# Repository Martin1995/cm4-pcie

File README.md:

# cm4-pcie
TODO:
-Connect HPD of HDMI In to the right pin on the Toshiba HDMI CSI-2 bridge

Feel free to copy the design, I'm not a Highspeed PCB expert, but if you want to use this PCB Design, to create a PCIe Card sized Raspberry Pi CM4 Carrier Board that can plug in to a PCIe Backplane feel free to do so.

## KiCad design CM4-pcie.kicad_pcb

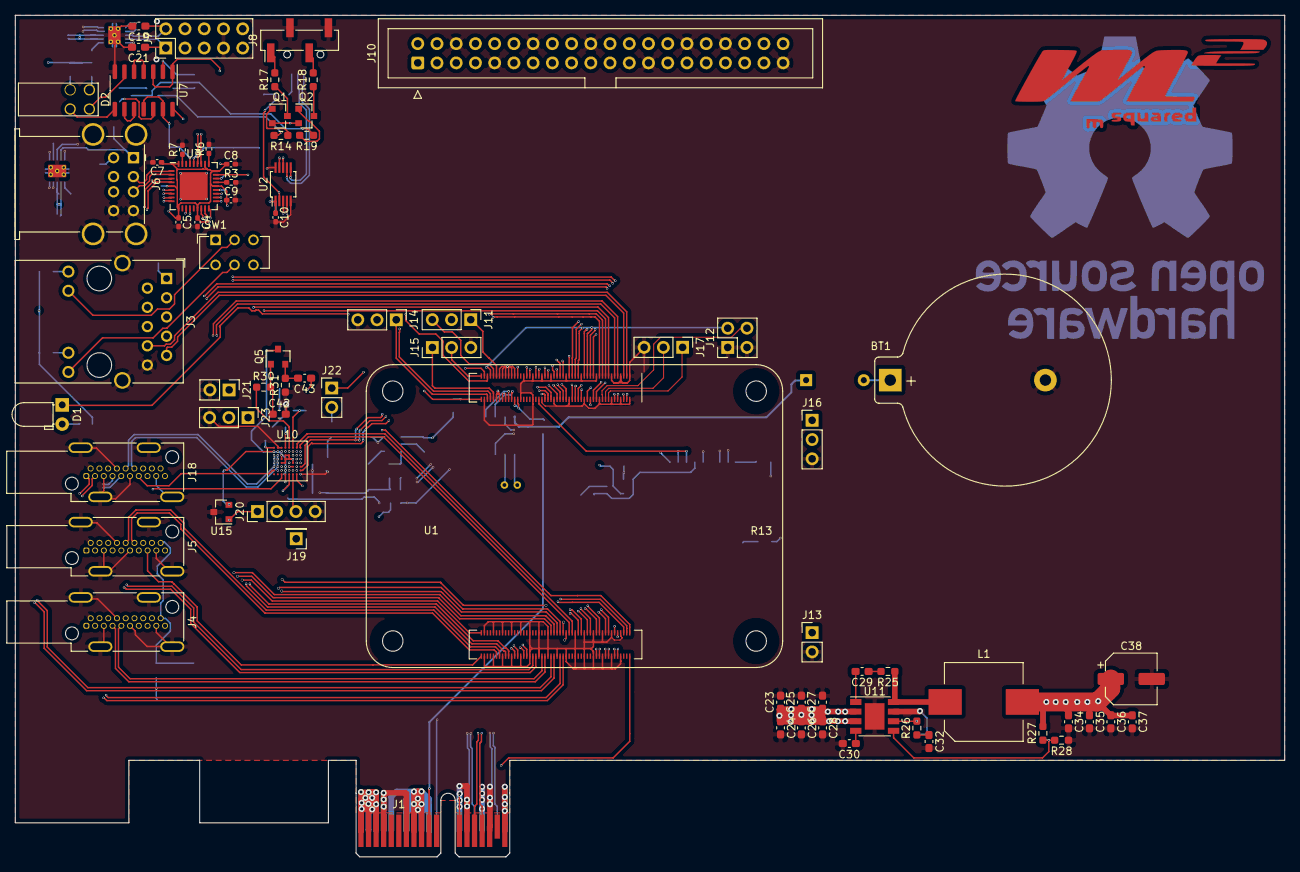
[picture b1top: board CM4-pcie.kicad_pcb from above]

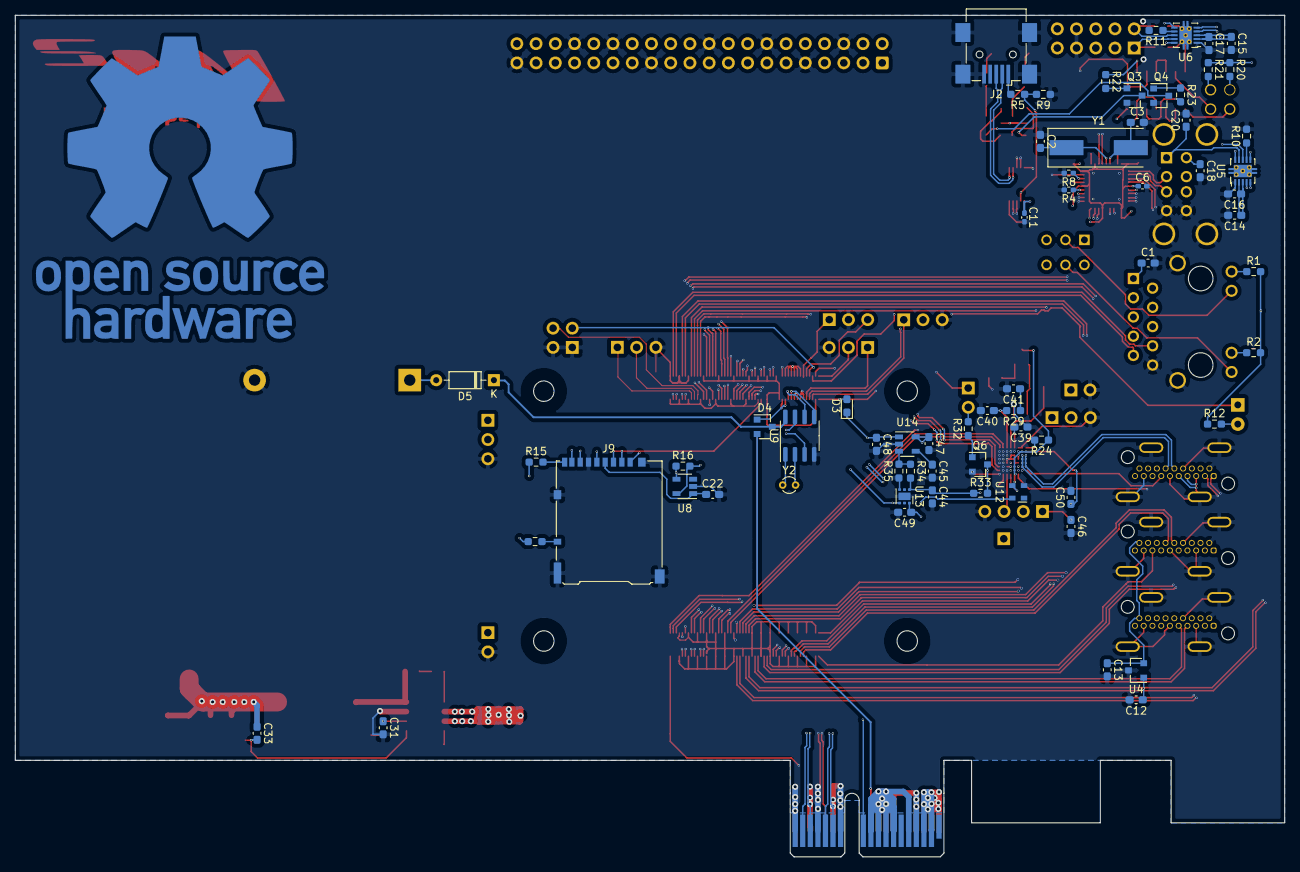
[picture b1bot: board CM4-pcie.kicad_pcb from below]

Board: 6 copper layers, 167.7 x 111.2 mm, 139 parts (66 on the bottom side), 226 nets.

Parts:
BT1: Battery_Cell; BatteryHolder_Keystone_106_1x20mm
C1: C; C_0603_1608Metric_Pad1.08x0.95mm_HandSolder
C2, C3: 27pF; C_0603_1608Metric_Pad1.08x0.95mm_HandSolder
C4, C5: 10µ; C_0402_1005Metric_Pad0.74x0.62mm_HandSolder
C6, C7, C8, C9, C10, C11: 100n; C_0402_1005Metric_Pad0.74x0.62mm_HandSolder
C12, C13, C29, C30: 100n; C_0603_1608Metric_Pad1.08x0.95mm_HandSolder
C14, C15, C16, C17, C18, C19, C20, C21, C22, C23, C24, C25, C26, C27, C28, C34, C35, C36, C37: 10µ; C_0603_1608Metric_Pad1.08x0.95mm_HandSolder
C31, C33: nf; C_0603_1608Metric_Pad1.08x0.95mm_HandSolder
C32: 1.2nF; C_0603_1608Metric_Pad1.08x0.95mm_HandSolder
C38: 100µF; CP_Elec_6.3x5.4_Nichicon
C39, C41: 0.1µF; C_0603_1608Metric_Pad1.08x0.95mm_HandSolder
C40, C43: 1000pF; C_0603_1608Metric_Pad1.08x0.95mm_HandSolder
C42: 5pF; C_0603_1608Metric_Pad1.08x0.95mm_HandSolder
C44, C46, C47, C48, C49, C50: 1µ; C_0603_1608Metric_Pad1.08x0.95mm_HandSolder
C45: 0.1µ; C_0603_1608Metric_Pad1.08x0.95mm_HandSolder
D1: LED; LED_D3.0mm_Horizontal_O1.27mm_Z2.0mm
D2: LED_Dual_AACC; DIAL_553-0112-20
D3: D; D_0603_1608Metric_Pad1.05x0.95mm_HandSolder
D4: BAT54C; SOT-23
D5: D_Schottky; D_DO-35_SOD27_P7.62mm_Horizontal
J1: Bus_PCI_Express_x1; BUS_PCIexpress_x1
J2: USB_B_Micro; USB_Mini-B_Wuerth_65100516121_Horizontal
J3: RB1-125B8G1A; RJ45_Wuerth_7499111446_Horizontal
J4, J5, J18: HDMI_A_1.4; HDMI_A_Kycon_KDMIX-SL1-NS-WS-B15_VerticalRightAngle
J6: USB_A; USB_A_Wuerth_61400826021_Horizontal_Stacked
J7: Conn_02x05_Odd_Even; PinHeader_2x05_P2.54mm_Vertical
J8: Conn_01x04; PinHeader_1x04_P2.54mm_Vertical_SMD_Pin1Left
J9: Micro_SD_Card_Det_Hirose_DM3AT; microSD_HC_Hirose_DM3AT-SF-PEJM5
J10: Raspberry_Pi_2_3; IDC-Header_2x20_P2.54mm_Vertical
J11, J14, J15, J16, J17, J23: Conn_01x03; PinHeader_1x03_P2.54mm_Vertical
J12: Conn_02x02_Odd_Even; PinHeader_2x02_P2.54mm_Vertical
J13, J21, J22: Conn_01x02; PinHeader_1x02_P2.54mm_Vertical
J19: Conn_01x01; PinHeader_1x01_P2.54mm_Vertical
J20: Conn_01x04; PinHeader_1x04_P2.54mm_Vertical
L1: 3.6µH WE7447797360; L_Wuerth_WE-PDF_Handsoldering
Q1, Q2: BC857; SOT-23
Q3, Q4, Q5, Q6: BC847; SOT-23
R1, R2, R12, R17, R18, R20, R21: 470R; R_0603_1608Metric_Pad0.98x0.95mm_HandSolder
R3, R4, R6, R8: 36k; R_0402_1005Metric_Pad0.72x0.64mm_HandSolder
R5, R9, R28: 2k2; R_0603_1608Metric_Pad0.98x0.95mm_HandSolder
R7: 12k; R_0402_1005Metric_Pad0.72x0.64mm_HandSolder
R10, R11: 28k; R_0603_1608Metric_Pad0.98x0.95mm_HandSolder
R13, R15: nf; R_0603_1608Metric_Pad0.98x0.95mm_HandSolder
R14, R19, R22, R23, R29, R31, R32, R33, R34, R35: 1k; R_0603_1608Metric_Pad0.98x0.95mm_HandSolder
R16: 12k; R_0603_1608Metric_Pad0.98x0.95mm_HandSolder
R24: 2k; R_0603_1608Metric_Pad0.98x0.95mm_HandSolder
R25: 10R; R_0603_1608Metric_Pad0.98x0.95mm_HandSolder
R26: 20k; R_0603_1608Metric_Pad0.98x0.95mm_HandSolder
R27: 10k; R_0603_1608Metric_Pad0.98x0.95mm_HandSolder
R30: 1k5; R_0603_1608Metric_Pad0.98x0.95mm_HandSolder
SW1: SW_DPDT_x2; SW_CuK_JS202011AQN_DPDT_Angled
U1: Compute_Module_4_Functional; Raspberry-Pi-4-Compute-Module
U2: FSUSB42MUX; MSOP-10_3x3mm_P0.5mm
U3: USB2514B_Bi; QFN-36-1EP_6x6mm_P0.5mm_EP3.7x3.7mm
U4, U15: RT9742SNGV; SOT-23
U5, U6: TPS2561; VSON-10-1EP_3x3mm_P0.5mm_EP1.65x2.4mm_ThermalVias
U7: 74HC04; SO-14_3.9x8.65mm_P1.27mm
U8: RT9742GGJ5; SOT-23-5
U9: PCF8563T; SOIC-8_3.9x4.9mm_P1.27mm
U10: TC358743XBG; TFBGA-64_5x5mm_Layout8x8_P0.5mm
U11: AP64501SP-13; Diodes_SO-8EP
U12: ASDMB-xxxMHz; Oscillator_SMD_Abracon_ASDMB-4Pin_2.5x2.0mm
U13: TLV75512PDRV; WSON-6-1EP_2x2mm_P0.65mm_EP1x1.6mm
U14: TC2015-2.5VxCTTR; SOT-23-5
Y1: Crystal; Crystal_SMD_HC49-SD
Y2: Crystal; Crystal_Round_D1.5mm_Vertical

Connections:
+1V2: C44.1, R33.1, R34.2, U10.B2, U10.C3, U10.C6, U10.D3, U10.F5, U10.F6, U10.G2, U13.1
+1V8: U1.88, U1.90, U12.4, U13.4
+2V5: C47.1, U10.B5, U14.5
+3.3VA: D4.2, J1.B10
+3V3: C4.1, C5.1, C6.1, C7.1, C8.1, C9.1, C10.1, C11.1, C46.1, C48.1, C49.1, D3.1, D4.1, J1.A5, J1.A7, J1.A8, J1.A9, J1.A10, J1.B8, J1.B9, J10.1, J10.17, J20.1, Q1.2, Q2.2, Q5.3, R1.2, R2.2, R12.1, R13.1, R16.2, R20.1, R21.1, R24.1, U1.78, U2.1, U3.5, U3.10, U3.15, U3.23, U3.27, U3.29, U3.36, U7.14, U8.5, U10.F4, U10.H7, U13.6, U14.1, U15.1
+3V3-HDMI: C50.1, U10.B1, U10.F3, U15.2
+5V: C12.1, C14.1, C15.1, C16.1, C17.1, C33.1, C34.1, C35.1, C36.1, C37.1, C38.1, J10.2, J10.4, L1.2, R27.2, U1.77, U1.79, U1.81, U1.83, U1.85, U1.87, U4.1, U5.2, U5.3, U6.2, U6.3
+12V: C23.1, C24.1, C25.1, C26.1, C27.1, C28.1, J1.A2, J1.A3, J1.B1, J1.B2, J1.B3, U11.2, U11.3
+BATT: BT1.1, D5.2
/LAN_LED1: D1.1, U1.19
/LAN_LED2: SW1.3, SW1.4, U1.17
/LAN_LED3: SW1.1, SW1.6, U1.15
/PCIe_CLK_N: J1.A14, U1.112
/PCIe_CLK_P: J1.A13, U1.110
/PCIe_RX_N: J1.A17, U1.118
/PCIe_RX_P: J1.A16, U1.116
/PCIe_TX_N: J1.B15, U1.124
/PCIe_TX_P: J1.B14, U1.122
/RJ45_LED1: J3.12, SW1.2
/RJ45_LED2: J3.14, SW1.5
/Sheet606D5A30/CM_USB_D+: U1.105, U2.3
/Sheet606D5A30/CM_USB_D-: U1.103, U2.4
/Sheet606D5A30/CM_USB_OTG: R5.1, R9.2, U1.101, U2.2
/Sheet606D5A30/HDMI0_CEC: J5.13, U1.151
/Sheet606D5A30/HDMI0_CLK_N: J5.12, U1.190
/Sheet606D5A30/HDMI0_CLK_P: J5.10, U1.188
/Sheet606D5A30/HDMI0_D0_N: J5.9, U1.184
/Sheet606D5A30/HDMI0_D0_P: J5.7, U1.182
/Sheet606D5A30/HDMI0_D1_N: J5.6, U1.178
/Sheet606D5A30/HDMI0_D1_P: J5.4, U1.176
/Sheet606D5A30/HDMI0_D2_N: J5.3, U1.172
/Sheet606D5A30/HDMI0_D2_P: J5.1, U1.170
/Sheet606D5A30/HDMI0_HOTPLUG: J5.19, U1.153
/Sheet606D5A30/HDMI0_SCL: J5.15, U1.200
/Sheet606D5A30/HDMI0_SDA: J5.16, U1.199
/Sheet606D5A30/HDMI1_CEC: J4.13, U1.149
/Sheet606D5A30/HDMI1_CLK_N: J4.12, U1.166
/Sheet606D5A30/HDMI1_CLK_P: J4.10, U1.164
/Sheet606D5A30/HDMI1_D0_N: J4.9, U1.160
/Sheet606D5A30/HDMI1_D0_P: J4.7, U1.158
/Sheet606D5A30/HDMI1_D1_N: J4.6, U1.154
/Sheet606D5A30/HDMI1_D1_P: J4.4, U1.152
/Sheet606D5A30/HDMI1_D2_N: J4.3, U1.148
/Sheet606D5A30/HDMI1_D2_P: J4.1, U1.146
/Sheet606D5A30/HDMI1_HOTPLUG: J4.19, U1.143
/Sheet606D5A30/HDMI1_SCL: J4.15, U1.147
/Sheet606D5A30/HDMI1_SDA: J4.16, U1.145
/Sheet606D5A30/HDMI_5v: C13.1, J4.18, J5.18, U4.2
/Sheet606D5A30/HUB_USB_D+: U2.9, U3.31
/Sheet606D5A30/HUB_USB_D-: U2.8, U3.30
/Sheet606D5A30/PROG_USB_D+: J2.3, U2.7
/Sheet606D5A30/PROG_USB_D-: J2.2, U2.6
/Sheet606D5A30/Sheet60CE0192/VBUS_P1: C20.1, J6.1, U5.9
/Sheet606D5A30/Sheet60CE0192/VBUS_P2: C18.1, J6.5, U5.8
/Sheet606D5A30/Sheet60CE0192/VBUS_P3: C21.1, J7.1, U6.9
/Sheet606D5A30/Sheet60CE0192/VBUS_P4: C19.1, J7.2, U6.8
/Sheet606E499F/BLUETOOTH_nDISABLE: J11.3, U1.91
/Sheet606E499F/EEPROM_nWP: J12.4, U1.20
/Sheet606E499F/RPI_ACT_LED: U1.21, U7.11, U7.13
/Sheet606E499F/RPI_PWR_LED: U1.95, U7.1, U7.3
/Sheet606E499F/Reserved: R15.1, U1.76
/Sheet606E499F/SD_CLK: J9.5, U1.57
/Sheet606E499F/SD_CMD: J9.3, U1.62
/Sheet606E499F/SD_DAT0: J9.7, U1.63
/Sheet606E499F/SD_DAT1: J9.8, U1.67
/Sheet606E499F/SD_DAT2: J9.1, U1.69
/Sheet606E499F/SD_DAT3: J9.2, U1.61
/Sheet606E499F/SD_PWR: C22.1, J9.4, U8.1
/Sheet606E499F/SD_PWR_ON: R16.1, U1.75, U8.4
/Sheet606E499F/WIRELESS_nDISABLE: J11.1, U1.89
/Sheet606E499F/nRPIBOOT: J12.2, U1.93
/Sheet611CBD44/CSI1_C_N: U1.127, U10.C7
/Sheet611CBD44/CSI1_C_P: U1.129, U10.C8
/Sheet611CBD44/CSI1_D0_N: U1.115, U10.E7
/Sheet611CBD44/CSI1_D0_P: U1.117, U10.E8
/Sheet611CBD44/CSI1_D1_N: U1.121, U10.D7
/Sheet611CBD44/CSI1_D1_P: U1.123, U10.D8
/Sheet611CBD44/CSI1_D2_N: U1.133, U10.B7
/Sheet611CBD44/CSI1_D2_P: U1.135, U10.B8
/Sheet611CBD44/CSI1_D3_N: U1.139, U10.A7
/Sheet611CBD44/CSI1_D3_P: U1.141, U10.A8
/Sheet611CBD44/HDMI_IN0_CEC: J18.13, U10.G1
/Sheet611CBD44/HDMI_IN0_CLK_N: J18.12, U10.C2
/Sheet611CBD44/HDMI_IN0_CLK_P: J18.10, U10.C1
/Sheet611CBD44/HDMI_IN0_D0_N: J18.9, U10.D2
/Sheet611CBD44/HDMI_IN0_D0_P: J18.7, U10.D1
/Sheet611CBD44/HDMI_IN0_D1_N: J18.6, U10.E2
/Sheet611CBD44/HDMI_IN0_D1_P: J18.4, U10.E1
/Sheet611CBD44/HDMI_IN0_D2_N: J18.3, U10.F2
/Sheet611CBD44/HDMI_IN0_D2_P: J18.1, U10.F1
/Sheet611CBD44/HDMI_IN0_EDID_SCL: J20.3, U10.H6
/Sheet611CBD44/HDMI_IN0_EDID_SDA: J20.2, U10.G6
/Sheet611CBD44/HDMI_IN0_HPD: J18.19, U10.H2
/Sheet611CBD44/HDMI_IN0_INT: J23.2, U10.B3
/Sheet611CBD44/HDMI_IN0_IR-IN: J21.1, U10.B4
/Sheet611CBD44/HDMI_IN0_SCL: J18.15, U10.H3
/Sheet611CBD44/HDMI_IN0_SDA: J18.16, U10.G3
/Sheet611CBD44/REFCLK0: U10.H5, U12.3
/Sheet611CBD44/RESETN: Q6.3, R33.2, U10.G5
/Sheet611CBD44/U10_BIASDA: C39.2, U10.A4
/Sheet611CBD44/U10_DAOUT: R30.1, U10.A5
/Sheet611CBD44/U10_PCKIN: C43.1, U10.B6
/Sheet611CBD44/U10_PFIL: C40.1, R29.2, U10.A6
/Sheet611CBD44/U10_TEST: J23.1, U10.E5
/Sheet6070FC9D/GPIO2: J10.3, U1.56
/Sheet6070FC9D/GPIO3: J10.5, U1.58
/Sheet6070FC9D/GPIO4: J10.7, U1.54
/Sheet6070FC9D/GPIO5: J10.29, U1.34
/Sheet6070FC9D/GPIO6: J10.31, U1.30
/Sheet6070FC9D/GPIO7: J10.26, U1.37
/Sheet6070FC9D/GPIO8: J10.24, U1.39
/Sheet6070FC9D/GPIO9: J10.21, U1.40
/Sheet6070FC9D/GPIO10: J10.19, U1.44
/Sheet6070FC9D/GPIO11: J10.23, U1.38
/Sheet6070FC9D/GPIO12: J10.32, U1.31
/Sheet6070FC9D/GPIO13: J10.33, U1.28
/Sheet6070FC9D/GPIO14: J10.8, U1.55
/Sheet6070FC9D/GPIO15: J10.10, U1.51
/Sheet6070FC9D/GPIO16: J10.36, U1.29
/Sheet6070FC9D/GPIO17: J10.11, U1.50
/Sheet6070FC9D/GPIO21: J10.40, U1.25
/Sheet6070FC9D/GPIO22: J10.15, U1.46
/Sheet6070FC9D/GPIO23: J10.16, U1.47
/Sheet6070FC9D/GPIO24: J10.18, U1.45
/Sheet6070FC9D/GPIO25: J10.22, U1.41
/Sheet6070FC9D/GPIO26: J10.37, U1.24
/Sheet6070FC9D/GPIO27: J10.13, U1.48
/Sheet6070FC9D/ID_SC: J10.28, U1.36
/Sheet6070FC9D/ID_SD: J10.27, U1.35
/TRD0_N: J3.3, U1.10
/TRD0_P: J3.2, U1.12
/TRD1_N: J3.5, U1.6
/TRD1_P: J3.4, U1.4
/TRD2_N: J3.7, U1.9
/TRD2_P: J3.6, U1.11
/TRD3_N: J3.9, U1.5
/TRD3_P: J3.8, U1.3
/__PCIe_CLK_nREQ: J1.B12, U1.102
/__PCIe_nRST: J1.A11, U1.109
AI0: J14.1, U1.96
AI1: J14.2, U1.94
CAM_GPIO: J22.1, U1.97
COMPOSITE: J13.1, U1.111
ETH_SYNC_IN: J17.1, U1.16
ETH_SYNC_OUT: J17.2, U1.18
GLOBAL_EN: J15.2, U1.99
GND: BT1.2, C1.2, C2.1, C3.2, C4.2, C5.2, C6.2, C7.2, C8.2, C9.2, C10.2, C11.2, C12.2, C13.2, C14.2, C15.2, C16.2, C17.2, C18.2, C19.2, C20.2, C21.2, C22.2, C23.2, C24.2, C25.2, C26.2, C27.2, C28.2, C30.2, C31.2, C32.2, C34.2, C35.2, C36.2, C37.2, C38.2, C39.1, C40.2, C41.2, C42.2, C44.2, C45.2, C46.2, C47.2, C48.2, C49.2, C50.2, J1.A4, J1.A12, J1.A15, J1.A18, J1.B4, J1.B7, J1.B13, J1.B16, J1.B18, J2.5, J2.6, J3.10, J3.SH, J4.2, J4.5, J4.8, J4.11, J4.17, J4.SH, J5.2, J5.5, J5.8, J5.11, J5.17, J5.SH, J6.4, J6.8, J6.9, J7.7, J7.8, J8.2, J8.4, J9.6, J9.11, J10.6, J10.9, J10.14, J10.20, J10.25, J10.30, J10.34, J10.39, J11.2, J12.1, J12.3, J13.2, J14.3, J15.3, J16.3, J17.3, J18.2, J18.5, J18.8, J18.11, J18.17, J18.SH, J20.4, J21.2, J23.3, Q3.2, Q4.2, Q6.2, R3.2, R4.2, R6.2, R7.2, R8.2, R9.1, R10.2, R11.2, R28.1, R31.1, R35.1, U1.1, U1.2, U1.7, U1.8, U1.13, U1.14, U1.22, U1.23, U1.32, U1.33, U1.42, U1.43, U1.52, U1.53, U1.59, U1.60, U1.65, U1.66, U1.71, U1.74, U1.98, U1.107, U1.108, U1.113, U1.114, U1.119, U1.120, U1.125, U1.126, U1.131, U1.132, U1.137, U1.138, U1.144, U1.150, U1.155, U1.156, U1.161, U1.162, U1.167, U1.168, U1.173, U1.174, U1.179, U1.180, U1.185, U1.186, U1.191, U1.192, U1.197, U1.198, U2.5, U2.10, U3.37, U4.3, U5.1, U5.11, U6.1, U6.11, U7.7, U8.2, U9.4, U10.A2, U10.A3, U10.C4, U10.C5, U10.D4, U10.D5, U10.D6, U10.E3, U10.E4, U10.E6, U10.H8, U11.7, U11.9, U12.2, U13.3, U13.7, U14.2, U15.3
HUB_USB_P1_D+: J6.3, U3.2
HUB_USB_P1_D-: J6.2, U3.1
HUB_USB_P1_PWR: U3.12, U5.4
HUB_USB_P1_nOC: U3.13, U5.10
HUB_USB_P2_D+: J6.7, U3.4
HUB_USB_P2_D-: J6.6, U3.3
HUB_USB_P2_PWR: U3.16, U5.5
HUB_USB_P2_nOC: U3.17, U5.6
HUB_USB_P3_D+: J7.3, U3.7
HUB_USB_P3_D-: J7.5, U3.6
HUB_USB_P3_PWR: U3.18, U6.4
HUB_USB_P3_nOC: U3.19, U6.10
HUB_USB_P4_D+: J7.4, U3.9
HUB_USB_P4_D-: J7.6, U3.8
HUB_USB_P4_PWR: U3.20, U6.5
HUB_USB_P4_nOC: U3.21, U6.6
I2S_A_OSCK: J19.1, U10.G7
I2S_A_SCK: J10.35, U1.26, U10.F7
I2S_A_SD: J10.12, U1.49, U10.F8
I2S_A_WFS: J10.38, U1.27, U10.G8
unnamed: C1.1, J3.1
unnamed: C2.2, U3.32, Y1.1
unnamed: C3.1, U3.33, Y1.2
unnamed: C29.1, R25.2
unnamed: C29.2, U11.1
unnamed: C30.1, U11.4
unnamed: C31.1, R26.2, U11.6
unnamed: C32.1, R26.1
unnamed: C33.2, R27.1, R28.2, U11.5
unnamed: C41.1, R29.1
unnamed: C42.1, Q5.1, R30.2
unnamed: C43.2, Q5.2, R31.2
unnamed: C45.1, U14.4
unnamed: D1.2, R12.2
unnamed: D2.1, U7.8
unnamed: D2.2, R20.2
unnamed: D2.3, U7.6
unnamed: D2.4, R21.2
unnamed: D3.2, U1.84, U1.86
unnamed: D4.3, D5.1, U9.8
unnamed: J2.1, R5.2
unnamed: J3.11, R1.1
unnamed: J3.13, R2.1
unnamed: J8.1, R17.2
unnamed: J8.3, R18.2
unnamed: J9.9, R15.2
unnamed: J9.10, R13.2
unnamed: J22.2, R32.2
unnamed: L1.1, R25.1, U11.8
unnamed: Q1.1, R14.1
unnamed: Q1.3, R17.1
unnamed: Q2.1, R19.2
unnamed: Q2.3, R18.1
unnamed: Q3.1, R22.2
unnamed: Q3.3, R14.2
unnamed: Q4.1, R23.1
unnamed: Q4.3, R19.1
unnamed: Q6.1, R32.1
unnamed: R3.1, U3.24
unnamed: R4.1, U3.22
unnamed: R6.1, U3.28
unnamed: R7.1, U3.35
unnamed: R8.1, U3.25
unnamed: R10.1, U5.7
unnamed: R11.1, U6.7
unnamed: R22.1, U7.2
unnamed: R23.2, U7.12
unnamed: R24.2, U10.A1
unnamed: R34.1, R35.2, U14.3
unnamed: U7.4, U7.5
unnamed: U7.9, U7.10
unnamed: U9.1, Y2.1
unnamed: U9.2, Y2.2
RTC_CLK_O: J16.1, U9.7
RTC_nINT: J16.2, U9.3
RUN_PG: J15.1, U1.92
SCL0: U1.80, U9.6, U10.H4
SDA0: U1.82, U9.5, U10.G4
nEXTRST: U1.100, U3.26

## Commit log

2021-04-14 initial upload
